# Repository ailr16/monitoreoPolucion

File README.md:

# monitoreoPolucion
Trabajo terminal. ESIME Z

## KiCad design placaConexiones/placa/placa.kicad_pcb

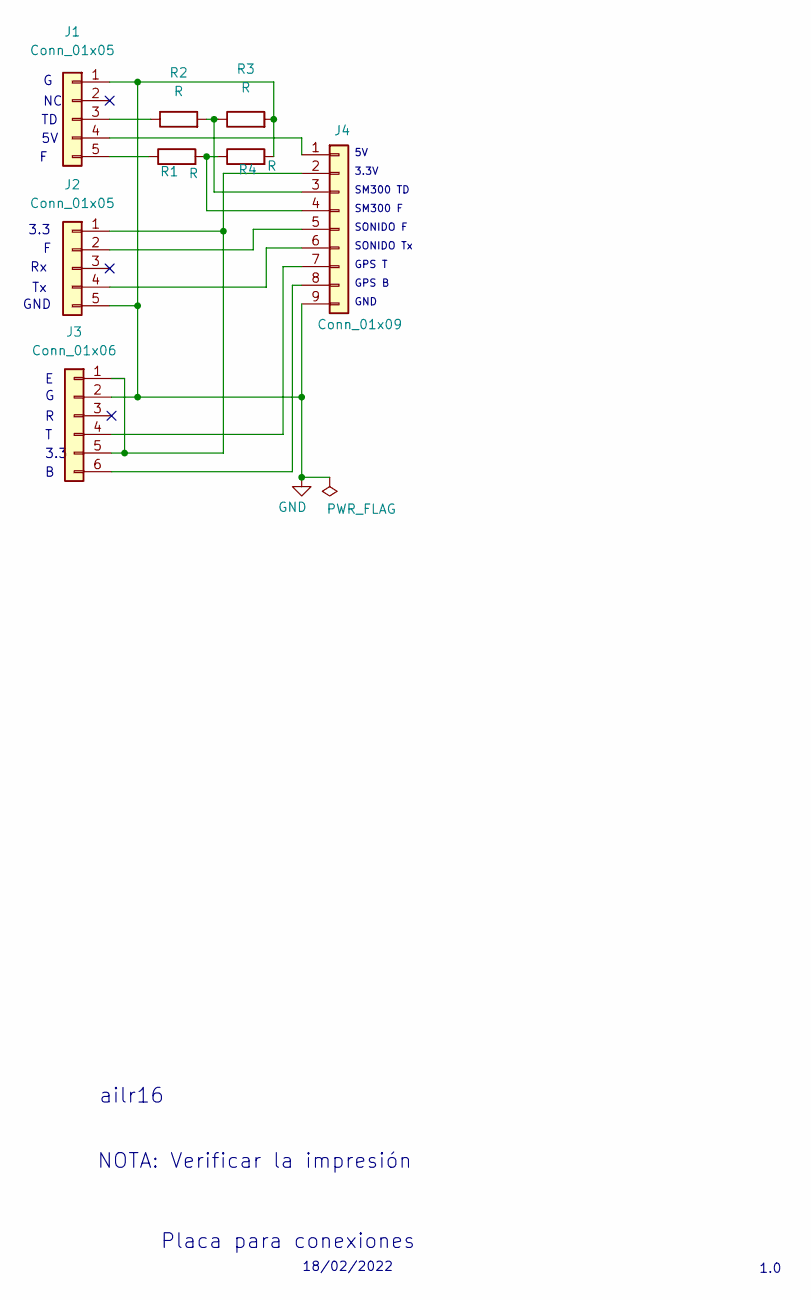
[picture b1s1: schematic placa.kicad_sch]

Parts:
J1, J2: Conn_01x05; PinHeader_1x05_P2.54mm_Vertical
J3: Conn_01x06; PinHeader_1x06_P2.54mm_Vertical
J4: Conn_01x09; PinHeader_1x09_P2.54mm_Vertical
R1, R2, R3, R4: R; R_Axial_DIN0207_L6.3mm_D2.5mm_P10.16mm_Horizontal

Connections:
GND: J1.1, J2.5, J3.2, J4.9, R3.2, R4.2
unnamed: J1.3, R2.1
unnamed: J1.4, J4.1
unnamed: J1.5, R1.1
unnamed: J2.1, J3.1, J3.5, J4.2
unnamed: J2.2, J4.5
unnamed: J2.4, J4.6
unnamed: J3.4, J4.7
unnamed: J3.6, J4.8
unnamed: J4.3, R2.2, R3.1
unnamed: J4.4, R1.2, R4.1

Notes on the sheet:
SONIDO F
GND
3.3
ailr16
3.3V
SONIDO Tx
Placa para conexiones
GPS T
NOTA: Verificar la impresión
1.0
18/02/2022
SM300 F
GPS B
SM300 TD

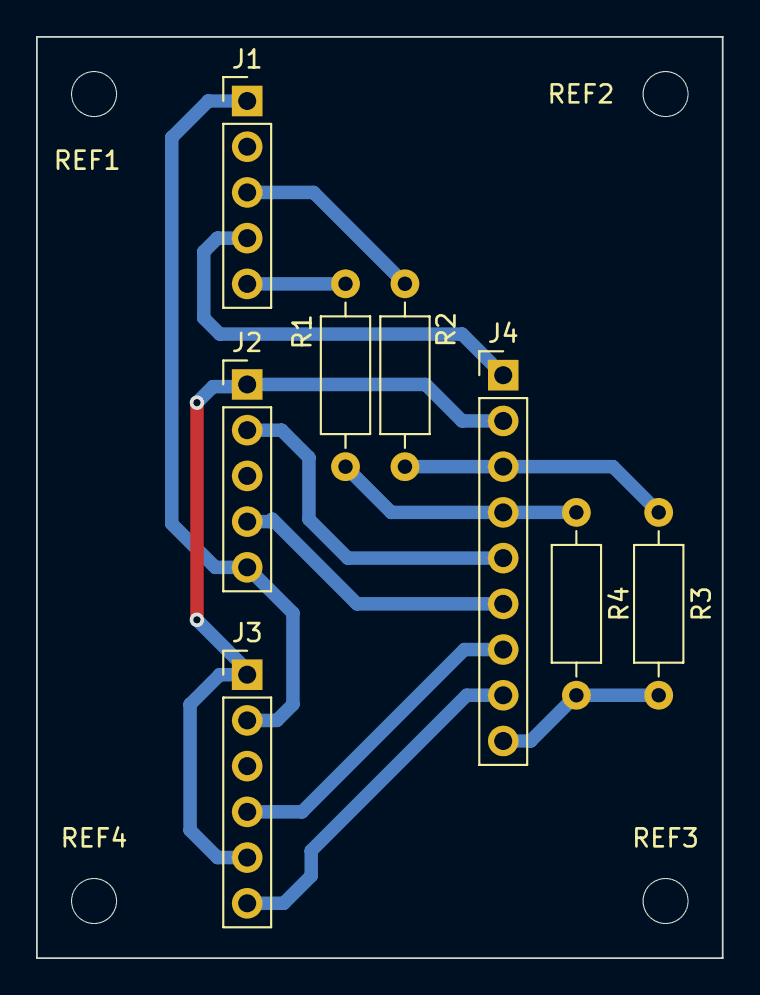
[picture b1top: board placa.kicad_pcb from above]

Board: 2 copper layers, 38.1 x 51.2 mm, 12 parts (0 on the bottom side), 11 nets.

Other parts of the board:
REF1, REF2, REF3, REF4: MountingHole_2.5mm

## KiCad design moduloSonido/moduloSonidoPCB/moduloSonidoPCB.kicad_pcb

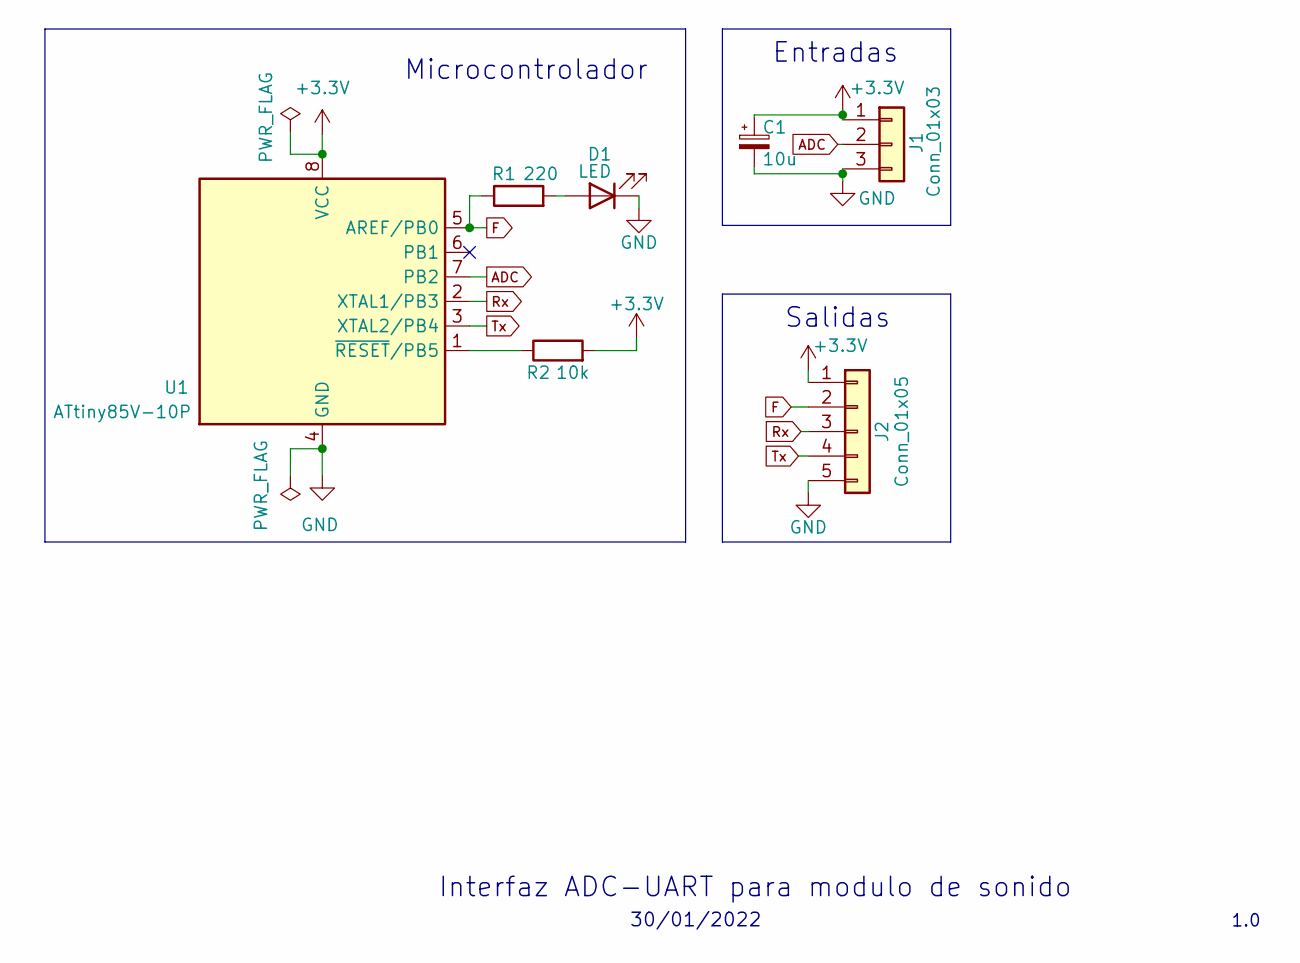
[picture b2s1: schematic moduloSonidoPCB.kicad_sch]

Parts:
C1: 10u; CP_Radial_D5.0mm_P2.50mm
D1: LED; LED_D3.0mm
J1: Conn_01x03; PinHeader_1x03_P2.54mm_Vertical
J2: Conn_01x05; PinHeader_1x05_P2.54mm_Vertical
R1: 220; R_Axial_DIN0207_L6.3mm_D2.5mm_P10.16mm_Horizontal
R2: 10k; R_Axial_DIN0207_L6.3mm_D2.5mm_P10.16mm_Horizontal
U1: ATtiny85V-10P; DIP-8_W7.62mm

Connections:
+3V3: C1.1, J1.1, J2.1, R2.2, U1.8 (VCC)
ADC: J1.2, U1.7 (PB2)
F: J2.2, R1.1, U1.5 (AREF/PB0)
GND: C1.2, D1.1 (K), J1.3, J2.5, U1.4 (GND)
unnamed: D1.2 (A), R1.2
unnamed: R2.1, U1.1 (~RESET/PB5)
Rx: J2.3, U1.2 (XTAL1/PB3)
Tx: J2.4, U1.3 (XTAL2/PB4)

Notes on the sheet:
30/01/2022
Entradas
Microcontrolador
Salidas
1.0
Interfaz ADC-UART para modulo de sonido

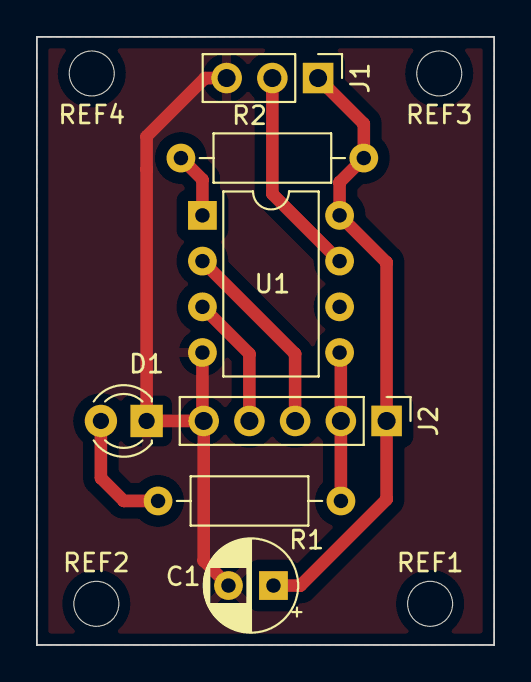
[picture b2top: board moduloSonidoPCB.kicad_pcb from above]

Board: 2 copper layers, 25.4 x 33.8 mm, 11 parts (0 on the bottom side), 8 nets.

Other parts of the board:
REF1, REF2, REF3, REF4: MountingHole_2.5mm

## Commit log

2022-01-12 Primera version con Azure
2022-01-14 Interrupciones
2022-01-14 Script funcionando dirigido por eventos (interrupcion en GPIO23)
2022-01-15 Gui integrada con interrupciones (falta GPS y sonido)
2022-01-16 Archivo de comandos para Azure
2022-01-30 Programa para ATTiny85
    Para implementar modulo de sonido con lectura analogica
2022-01-31 Diseño PCB
    KiCad :+1:
2022-02-05 Respaldo para actualizacion de SO 64
2022-02-06 Actualizacion de archivo con datos importantes
2022-02-06 Correcion de nombre
2022-02-06 Archivos pcb
2022-02-06 Script para leer modulo de sonido
2022-02-06 PCB 1.1
    Capacitor y plano de tierra agregados
2022-02-06 Update sample time ATTiny85
    500ms to 1000ms
2022-02-06 Actualizacion PCB
    Algunos cambios en diseño de PCB
2022-02-09 Error corregido en la PCB
2022-02-09 Organizacion en carpetas - Modelos del gabinete
2022-02-10 PCB para conexiones
2022-02-10 Cambios en diseños (PCB y Gabinete)
2022-02-12 Cambios en modelos 3d
    Principal version final :100:
    Sensores primera version, todavia no esta lista
2022-02-12 Correccion en el gabinete
2022-02-13 Avances en el gabinete :+1:
2022-02-13 Cambios en el gabinete
2022-02-15 Preparado modulo para sensores
    Para imprimir 3d
2022-02-15 Error en modelo para sensores, corregido
2022-02-15 Modelos preparados para imprimir
    :100:
2022-02-16 Reorganizacion y cambios en cubierta
2022-02-17 Cambios en modelos
    -Cubierta dividida en dos partes
    -Reorganizacion en carpetas
2022-02-17 Generados archivos PDF para PCB
2022-02-17 gabinete v2.1
    Retirados los rieles
2022-02-18 Correccion modelo principal
2022-02-19 Actualizacion esquematico de placa
2022-02-19 Modelo sensores v2.1
    Mejoras en el diseño para reducir el tiempo de impresion
2022-02-19 Preparacion ultima parte gabinete v2.1
2022-02-20 Pieza para sujetar cable
2022-02-21 Depuracion del codigo
    Regresando a thingspeak
    Revision de nombres de variable
    Reorganizacion de funciones
2022-02-21 Script para verficar acceso a internet
2022-02-21 Script para verificar conexion a wifi
2022-02-21 Actualizacion script wifi
2022-02-21 Actualizacion script principal
    Añadidos bloques en caso de no contar con conexion wifi
2022-02-21 Correcion error skip -> pass
2022-03-02 ACtualizaciones de scripts
2022-03-02 Prueba con modulo de sonido y GPS a la vez
2022-03-02 Comenzando ewl script final
2022-03-17 Actualizacion key GitHub
2022-03-17 Agregado wallpaper y carpeta otros
2022-03-17 Actualizacion rangos spl
2022-03-17 Actualizacion
2022-03-17 CAmbio pequeño
2022-03-17 Creacion archivo key thingspeak
2022-03-17 Pruebas de lectura de key ThingSpeak y envio al servidor
2022-03-17 Actualizacion scriptFinal
2022-03-17 Muestreo de 15 segundos
2022-03-17 Corregido error muestreo
2022-03-17 Caso offline, lectura de la key de thingspeak, guardar ultima posicion gps
2022-03-17 Redondear latitud y longitud a 6 decimales
2022-03-17 Actualizado contador inicial de eventos y formato de spl
2022-03-17 Correcion error gps
2022-03-17 Redondeo a 5 decimales
2022-03-17 Eliminar key para evitar errores futuros
2022-03-17 Ultima actualizacion RPi
2022-03-17 Git ignore
2022-03-17 Actualizacion valor inicial del contador de eventos
2022-03-18 Cambios modelos y diseños
2022-03-27 Primer Actualizacion dibujos
2022-03-28 Actualizacion planos
2022-04-05 Cambios diagramas
2022-04-22 Comentarios
2022-05-09 Renders para manual
    :hocho:
2022-05-22 Croquis de la pieza cubierta
2022-05-22 Croquis alimentacion
2023-02-06 new branch
2023-02-06 agregada key thingspeak al repo
2023-02-06 Agregado soporte para Ethernet y debug por terminal
2023-03-20 Final srcipt with terminal debugging
2023-03-20 Script final debugging SPLDIS
2023-03-20 debugging SPL_DIS
2023-03-20 debugging SPL_GPS_DIS
2023-03-20 debug SPL_GPS_DIS
2023-03-20 SM_GPS_EN_SPL_DIS
2023-03-20 SmSpl_EN_Gps_DIS
2023-03-20 SplSerial_DIS
2023-03-20 debug
2023-03-20 debug SPL
2023-03-20 spl debug
2023-03-20 debug SPL UART4
2023-03-20 debug GPS
2023-03-20 Final script
2023-04-23 Final version
